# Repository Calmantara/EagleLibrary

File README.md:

# Eagle Library

This repository for PCB design using EAGLE software. The specification is board size must be small.

The components are:
1. ATMega 328 SMD
2. ESP WROOM 02
3. DC-DC Stepdown MP2307
4. SD Card Module
5. Zener Diode
6. Jumper
7. Push Button
8. Capacitor
9. Resistor
10. Variable Resistor
11. Fuse

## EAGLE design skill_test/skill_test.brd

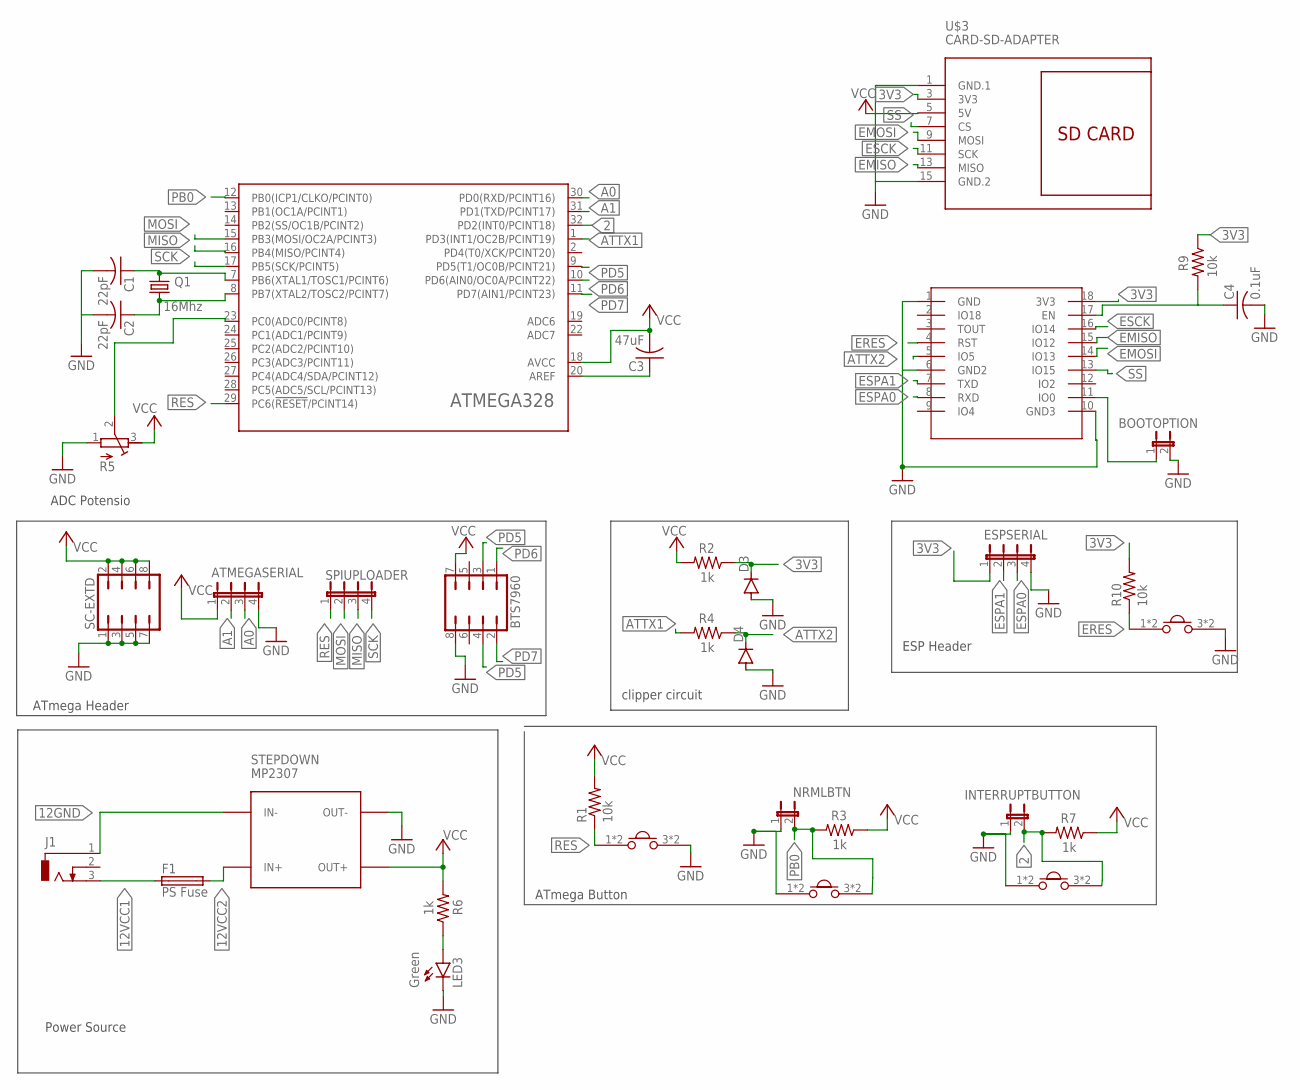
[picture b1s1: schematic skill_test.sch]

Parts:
2: SMD-PUSHBUTTON
ATMEGA328: ATMEGA48/88/168/328-AU; TQFP32-08
ATMEGASERIAL: JP4E; JP4
BOOTOPTION: JP1E; JP1
BTS7960: JP4Q
C1, C2: 22pF; C0805
C3: 47uF; C0805
C4: 0.1uF; C025-024X044
D3, D4: BAT81; DO34-7
ESPSERIAL: JP4E; JP4
F1: PS Fuse; FUSE_HOLDER_5X20MM
INTERRUPTBUTTON: JP1E; JP1
J1: DCJ0303
LED3: Green; LED3MM
NRMLBTN: JP1E; JP1
PB0: SMD-PUSHBUTTON
Q1: 16Mhz; HC49UP
R1, R10: 10k; R0805
R2, R3, R4, R6, R7: 1k; 0204/7
R5: R-TRIMM64W; RTRIM64W
R9: 10k; 0204/7
RES: SMD-PUSHBUTTON
SC-EXTD: JP4Q
SPIUPLOADER: JP4E; JP4
STEPDOWN: MP2307; DC-DC-STEP-DOWN-MP2307
U$1: ESP-WROOM-02
U$3: CARD-SD-ADAPTER
U$6: SMD-PUSHBUTTON

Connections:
2: 2.3 (2), 2.4 (2), ATMEGA328.32 (PD2(INT0/PCINT18)), INTERRUPTBUTTON.2, R7.2
3V3: D3.C, ESPSERIAL.1, R2.1, R9.1, R10.2, U$1.18 (3V3), U$3.3 (3V3)
12GND: J1.1, STEPDOWN.IN-
12VCC1: F1.1, J1.3
12VCC2: F1.2, STEPDOWN.IN+
A0: ATMEGA328.30 (PD0(RXD/PCINT16)), ATMEGASERIAL.3
A1: ATMEGA328.31 (PD1(TXD/PCINT17)), ATMEGASERIAL.2
ATTX1: ATMEGA328.1 (PD3(INT1/OC2B/PCINT19)), R4.2
ATTX2: D4.C, R4.1, U$1.5 (IO5)
EMISO: U$1.15 (IO12), U$3.13 (MISO)
EMOSI: U$1.14 (IO13), U$3.9 (MOSI)
ERES: R10.1, U$1.4 (RST), U$6.1, U$6.2 (1)
ESCK: U$1.16 (IO14), U$3.11 (SCK)
ESPA0: ESPSERIAL.3, U$1.8 (RXD)
ESPA1: ESPSERIAL.2, U$1.7 (TXD)
GND: 2.1, 2.2 (1), ATMEGA328.3 (GND), ATMEGA328.5 (GND), ATMEGA328.21 (GND), ATMEGASERIAL.4, BOOTOPTION.2, BTS7960.8, C1.2, C2.2, C4.2, D3.A, D4.A, ESPSERIAL.4, INTERRUPTBUTTON.1, LED3.K (C), NRMLBTN.1, PB0.1, PB0.2 (1), R5.1 (A), RES.3 (2), RES.4 (2), SC-EXTD.1, SC-EXTD.3, SC-EXTD.5, SC-EXTD.7, STEPDOWN.OUT-, U$1.1 (GND), U$1.6 (GND2), U$1.10 (GND3), U$3.1 (GND.1), U$3.15 (GND.2), U$6.3 (2), U$6.4 (2)
MISO: ATMEGA328.16 (PB4(MISO/PCINT4)), SPIUPLOADER.3
MOSI: ATMEGA328.15 (PB3(MOSI/OC2A/PCINT3)), SPIUPLOADER.2
unnamed: LED3.A, R6.1
unnamed: ATMEGA328.20 (AREF), C3.1
unnamed: ATMEGA328.8 (PB7(XTAL2/TOSC2/PCINT7)), C2.1, Q1.2
unnamed: ATMEGA328.7 (PB6(XTAL1/TOSC1/PCINT6)), C1.1, Q1.1
unnamed: ATMEGA328.23 (PC0(ADC0/PCINT8)), R5.2 (S)
unnamed: BOOTOPTION.1, U$1.11 (IO0)
unnamed: C4.1, R9.2, U$1.17 (EN)
PB0: ATMEGA328.12 (PB0(ICP1/CLKO/PCINT0)), NRMLBTN.2, PB0.3 (2), PB0.4 (2), R3.2
PD5: ATMEGA328.9 (PD5(T1/OC0B/PCINT21)), BTS7960.3, BTS7960.4
PD6: ATMEGA328.10 (PD6(AIN0/OC0A/PCINT22)), BTS7960.1
PD7: ATMEGA328.11 (PD7(AIN1/PCINT23)), BTS7960.2
RES: ATMEGA328.29 (PC6(!RESET!/PCINT14)), R1.1, RES.1, RES.2 (1), SPIUPLOADER.1
SCK: ATMEGA328.17 (PB5(SCK/PCINT5)), SPIUPLOADER.4
SS: U$1.13 (IO15), U$3.7 (CS)
UCC: ATMEGA328.4 (UCC), ATMEGA328.6 (UCC)
VCC: ATMEGA328.18 (AVCC), ATMEGASERIAL.1, BTS7960.7, C3.2, R1.2, R2.2, R3.1, R5.3 (E), R6.2, R7.1, SC-EXTD.2, SC-EXTD.4, SC-EXTD.6, SC-EXTD.8, STEPDOWN.OUT+, U$3.5 (5V)

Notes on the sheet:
Power Source
ADC Potensio
clipper circuit
ATmega Header
ATmega Button
ESP Header

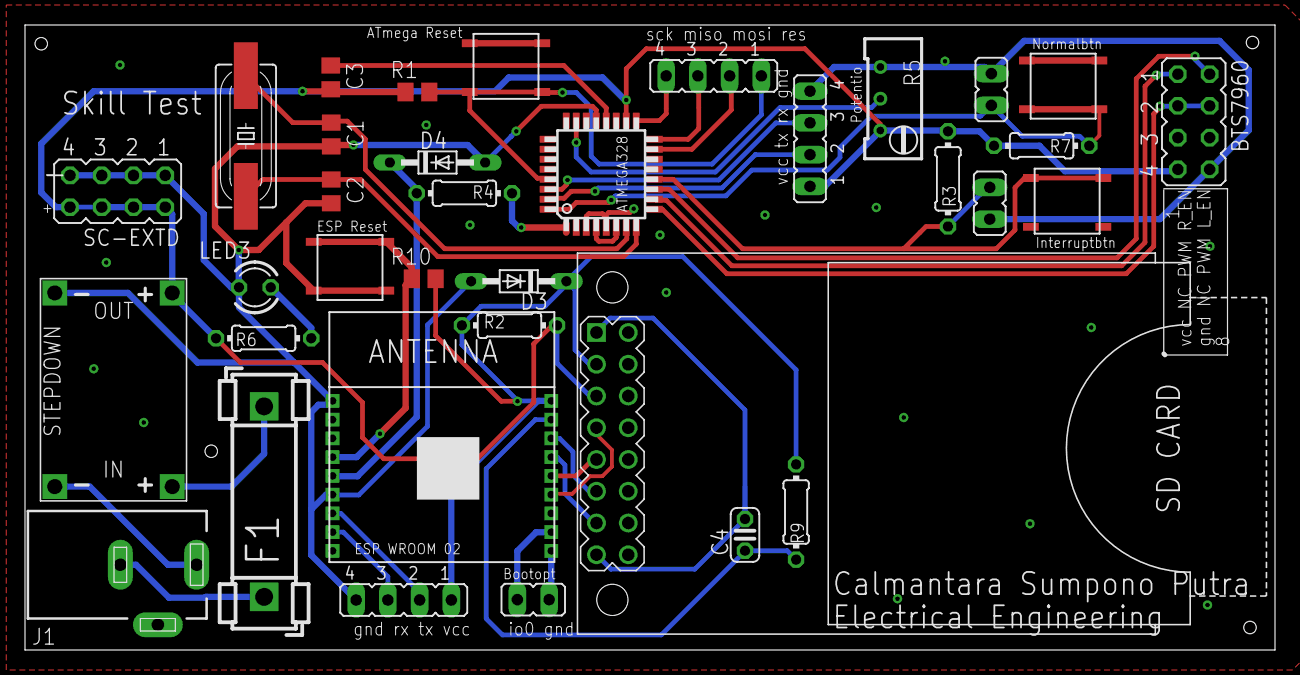
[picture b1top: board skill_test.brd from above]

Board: 2 copper layers, 100.0 x 50.0 mm, 35 parts (0 on the bottom side), 34 nets.

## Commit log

2020-05-17 add repository files
2020-05-17 update route
2020-05-17 fixed route
2020-05-18 Fixed pin mapping from ESP
2021-02-17 refactor readme

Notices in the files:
parts and their libraries:
diy-modules: Released under the Creative Commons Attribution 4.0 International License: http://creativecommons.org/licenses/by/4.0
